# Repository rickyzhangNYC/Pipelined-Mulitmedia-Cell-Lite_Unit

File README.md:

# Three stage pipelined multimedia cell lite unit
## Project Goal
The main goal of our project is to use VHDL , a hardware description language in order 
to design the behavior of a triple stage pipelined multimedia Cell-Lite unit with reduced 
multimedia functions just like how it was done in the Sony Cell SPU architecture. 
The use of cad tools such as a VHDL/Verilog simulator was used to test our results. 
In our case, we used Aldec Active HDL simulator to write and test our code in VHDL.

## Procedure
In order to implement the Three-stage pipelined Cell-lite unit, we first implemented the ALU. 
The ALU consisted of two major sub-modules, each with different functions. 
These modules are the arithmetic module which consist of the adding and subtractions functions 
and the logic and shift module which consist of all the logic and shift operations.  
In order to do the arithmetic module, we needed to create a 16-bit/32-bit arithmetic module 
using a triple level carry look ahead system. We tested our carry-look ahead system using the 
simulation in AHDL. We input values into our registers and using a mux to select whether 
it was addition or subtraction, we tested our CLA. 

## Required OP Code functionality
|OPCODE 3-0 | Description of Instruction Opcode |
| --- | --- |
|0000 |	nop |
|0001 | lv: Load a 8-bit immediate value from the [11:4] instruction field into the every byteof register rd.(This is done by bypassing the ALUs arithmetic and logical/shift modules. The lv 'execution" takes the same amount of time as all other operations.) |
|0010 | and: bitwise logical and of the contents of registers rs1 and rs2 |
|0011 | or: bitwise logical or of the contents of registers rs1 and rs2 |
|0100 | cnth: count ones in halfwords: the number of 1s in each of the four halfword-slots in register rs1 is computed. If the halfword slot in register rs1 is zero, the result is 0. Each of the results is placed into corresponding 16-bit slot in register rd. (Comments: 4 separate 16-bit halfword values  in each 64-bit register) |
|0101 | clz: count leading zeroes in words: for each of the two 32-bit word slots in register rs1 the number of zero bits to the left of the first 1 is computed. If the word slot in register rs1 is zero, the result is 32. The two results are placed into the corresponding 32-bit word slots in register rd. (Comments: 2 separate 32-bit values in each 64-bit register) |
|0110 | rot: rotate right: the contents of register rs1 are rotated to the right according to the count in the 6 least significant bits (5 to 0) of the contents of register rs2. The result is placed in register rd. If the count is zero, the contents of register rs1 are copied unchanged into register rd. Bits rotated out of the right end of the 64-bit contents of register rs1 are rotated in at the left end. |
|0111 | shlhi: shift left halfword immediate: packed 16-bit halfword shift left logical of the contents of register rs1 by the 4-bit immediate value of instruction field rs2. Each of the results is placed into the corresponding 16-bit slot in register rd. (Comments: 4 separate 16-bit values in each 64-bit register) |
|1000 | a: add word: packed 32-bit unsigned add of the contents of registers rs1 and rs2 (Comments: 2 separate 32-bit values in each 64-bit register) |
|1001 | sfw: subtract from word: (packed) 32-bit unsigned subtract of the contents of registers rs1 and rs2 (Comments: 2 separate 32-bit values in each 64-bit register) |
|1010 | ah: add halfword : (packed) (16-bit) halfword unsigned add of the contents of registers rs1 and rs2 (Comments: 4 separate 16-bit values in each 64-bit register) |
|1011 | sfh: subtract from halfword: (packed) (16-bit) halfword unsigned subtract of the contents of registers rs1 and rs2 |
|1100 | ahs: add halfword saturated: (packed) (16-bit) halfword unsigned add with saturation of the contents of registers rs1 and rs2 |
|1101 | sfhs: subtract from halfword saturated: (packed) (16-bit) unsigned subtract with saturation of the contents of registers rs1 and rs2 |
|1110 | mpyu:  multiply unsigned: the 16 rightmost bits of each of the two 32-bit slots in registers rs1 are multiplied by the 16 rightmost bits of the corresponding 32-bit slots in register rs2, treating both operands as unsigned. The two 32-bit products are placed into the corresponding slots of register rd. (Comments: 2 separate 32-bit values in each 64-bit register) |
|1111 | absdb:  absolute difference of bytes: the contents of each of the eight byte slots in register rs2 is subtracted from the contents of the corresponding byte slot in register rs1. The absolute value of each of the results is placed into the corresponding byte slot in register rd. (Comments: 8 separate 8-bit values in each 64-bit register) |

## Synthesized hardware circuit design:

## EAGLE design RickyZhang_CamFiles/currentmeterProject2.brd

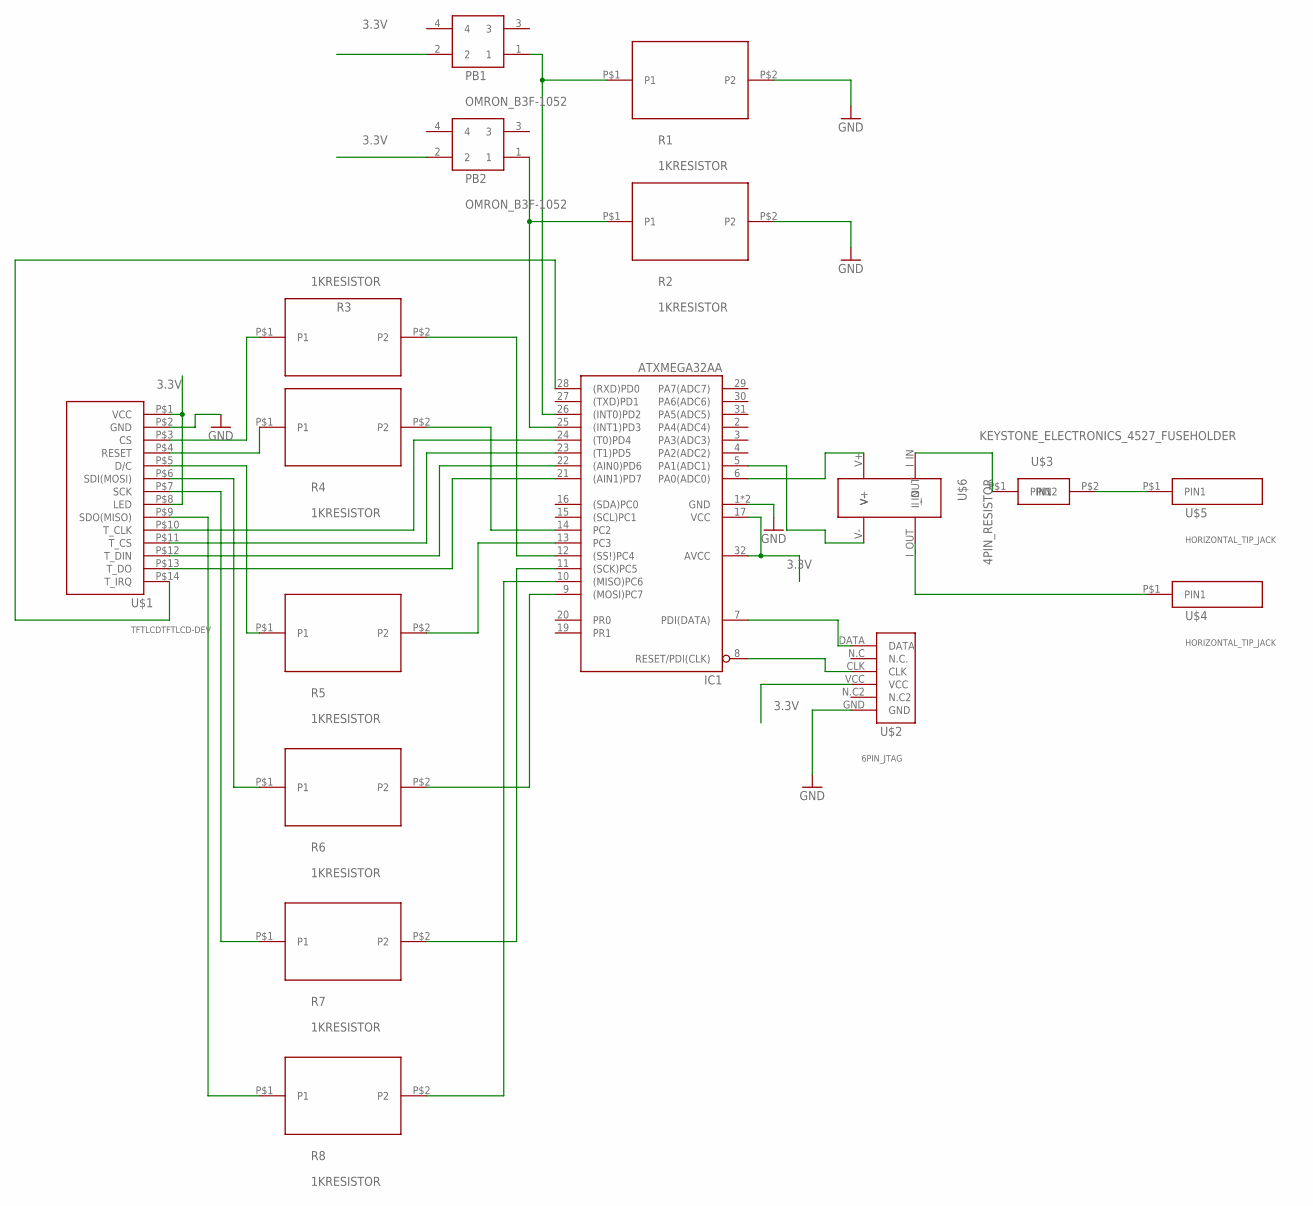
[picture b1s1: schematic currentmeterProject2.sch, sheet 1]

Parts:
IC1: ATXMEGA32AA; TQFP32-08
PB1, PB2: OMRON_B3F-1052
R1, R2, R3, R4, R5, R6, R7, R8: 1KRESISTOR
U$1: TFTLCDTFTLCD-DEV
U$2: 6PIN_JTAG
U$3: KEYSTONE_ELECTRONICS_4527_FUSEHOLDER
U$4, U$5: HORIZONTAL_TIP_JACK
U$6: 4PIN_RESISTOR

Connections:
3.3V: IC1.17 (VCC), IC1.32 (AVCC), PB1.2, PB2.2, U$1.P$1 (VCC), U$1.P$8 (LED), U$2.VCC; also elsewhere on the board
GND: IC1.1 (GND), IC1.18 (GND), R1.P$2 (P2), R2.P$2 (P2), U$1.P$2 (GND), U$2.GND; also elsewhere on the board
unnamed: IC1.5 (PA1(ADC1)), U$6.V-
unnamed: IC1.6 (PA0(ADC0)), U$6.V+
unnamed: U$3.P$1 (PIN1), U$6.I_IN
unnamed: U$3.P$2 (PIN2), U$5.P$1
unnamed: U$4.P$1, U$6.I_OUT
unnamed: IC1.7 (PDI(DATA)), U$2.DATA
unnamed: IC1.8 (RESET/PDI(CLK)), U$2.CLK
unnamed: IC1.12 ((SS!)PC4), R3.P$2 (P2)
unnamed: IC1.28 ((RXD)PD0), U$1.P$14 (T_IRQ)
unnamed: IC1.14 (PC2), R4.P$2 (P2)
unnamed: IC1.13 (PC3), R5.P$2 (P2)
unnamed: IC1.9 ((MOSI)PC7), R6.P$2 (P2)
unnamed: IC1.11 ((SCK)PC5), R7.P$2 (P2)
unnamed: IC1.10 ((MISO)PC6), R8.P$2 (P2)
unnamed: R3.P$1 (P1), U$1.P$3 (CS)
unnamed: R4.P$1 (P1), U$1.P$4 (RESET)
unnamed: R5.P$1 (P1), U$1.P$5 (D/C)
unnamed: R6.P$1 (P1), U$1.P$6 (SDI(MOSI))
unnamed: R7.P$1 (P1), U$1.P$7 (SCK)
unnamed: R8.P$1 (P1), U$1.P$9 (SDO(MISO))
unnamed: IC1.24 ((T0)PD4), U$1.P$10 (T_CLK)
unnamed: IC1.23 ((T1)PD5), U$1.P$11 (T_CS)
unnamed: IC1.22 ((AIN0)PD6), U$1.P$12 (T_DIN)
unnamed: IC1.21 ((AIN1)PD7), U$1.P$13 (T_DO)
unnamed: IC1.25 ((INT1)PD3), PB2.1, R2.P$1 (P1)
unnamed: IC1.26 ((INT0)PD2), PB1.1, R1.P$1 (P1)

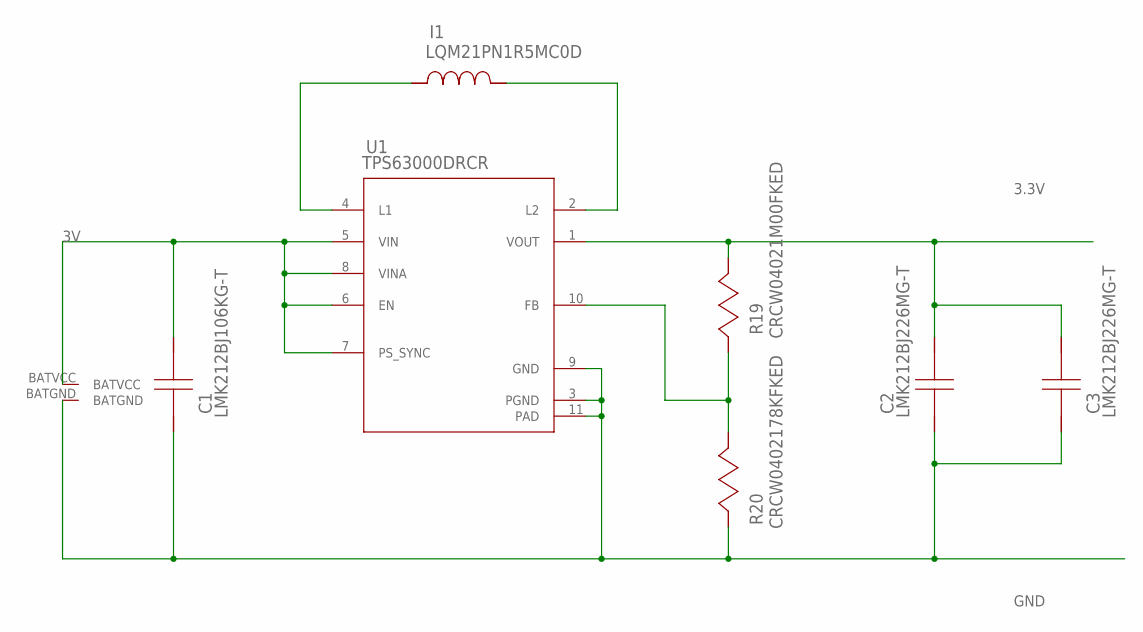
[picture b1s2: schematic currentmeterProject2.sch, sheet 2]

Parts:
C1: LMK212BJ106KG-T; 0805
C2, C3: LMK212BJ226MG-T; 0805
I1: LQM21PN1R5MC0D; 0805
R19: CRCW04021M00FKED; 0402
R20: CRCW0402178KFKED; 0402
U1: TPS63000DRCR; DRC0010J
U$12: BATTERYHOLDER

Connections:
3.3V: C2.1, C3.1, R19.1, U1.1 (VOUT); also elsewhere on the board
3V: C1.1, U1.5 (VIN), U1.6 (EN), U1.7 (PS_SYNC), U1.8 (VINA), U$12.BATVCC
GND: C1.2, C2.2, C3.2, R20.2, U1.3 (PGND), U1.9 (GND), U1.11 (PAD), U$12.BATGND; also elsewhere on the board
unnamed: I1.1, U1.4 (L1)
unnamed: I1.2, U1.2 (L2)
unnamed: R19.2, R20.1, U1.10 (FB)

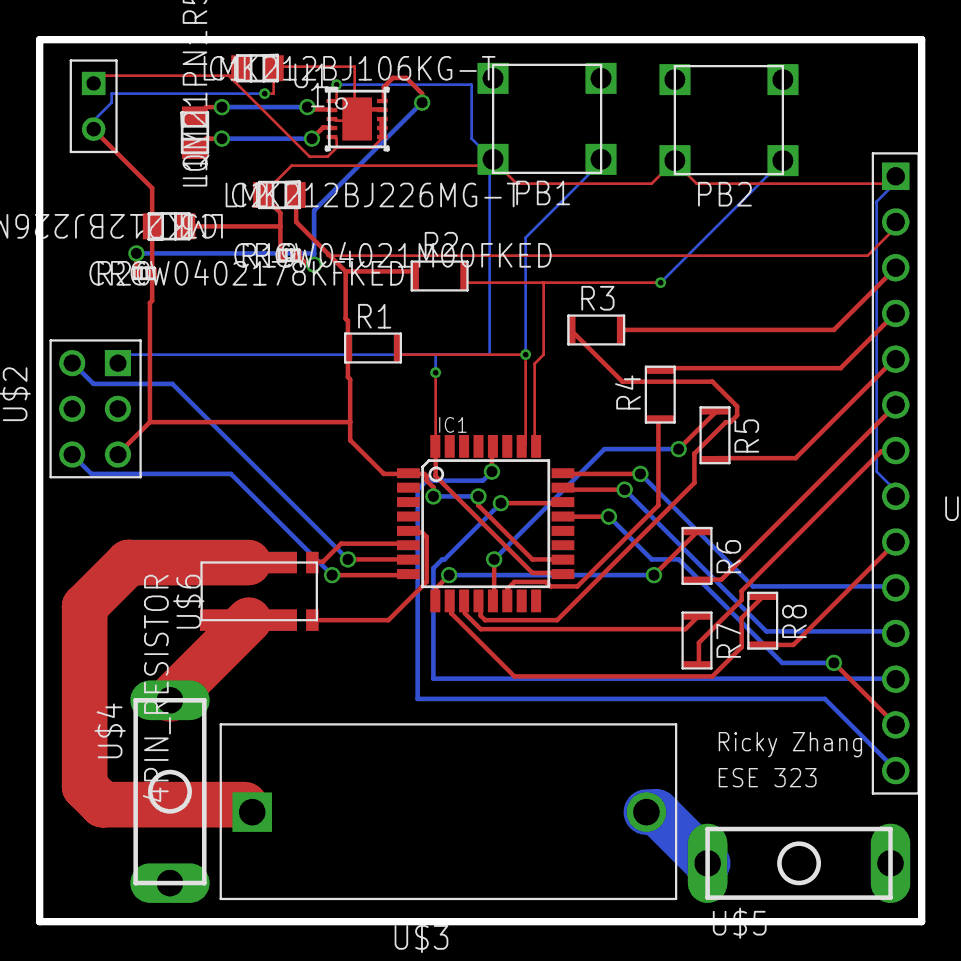
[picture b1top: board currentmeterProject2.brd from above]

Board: 2 copper layers, 49.0 x 49.0 mm, 25 parts (0 on the bottom side), 32 nets.

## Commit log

2018-07-10 Uploaded images
2018-07-10 updated pictures
2018-07-10 updated table
2018-07-10 update table v2
2018-07-10 table v3
